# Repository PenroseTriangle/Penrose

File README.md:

The Penrose Triangle
====================

http://penrosetriangle.com/wordpress/

Hardware and software for the Penrose Triangle, a 2013 Burning Man Honorarium Project.

pcb: Eagle PCB layouts, etc.

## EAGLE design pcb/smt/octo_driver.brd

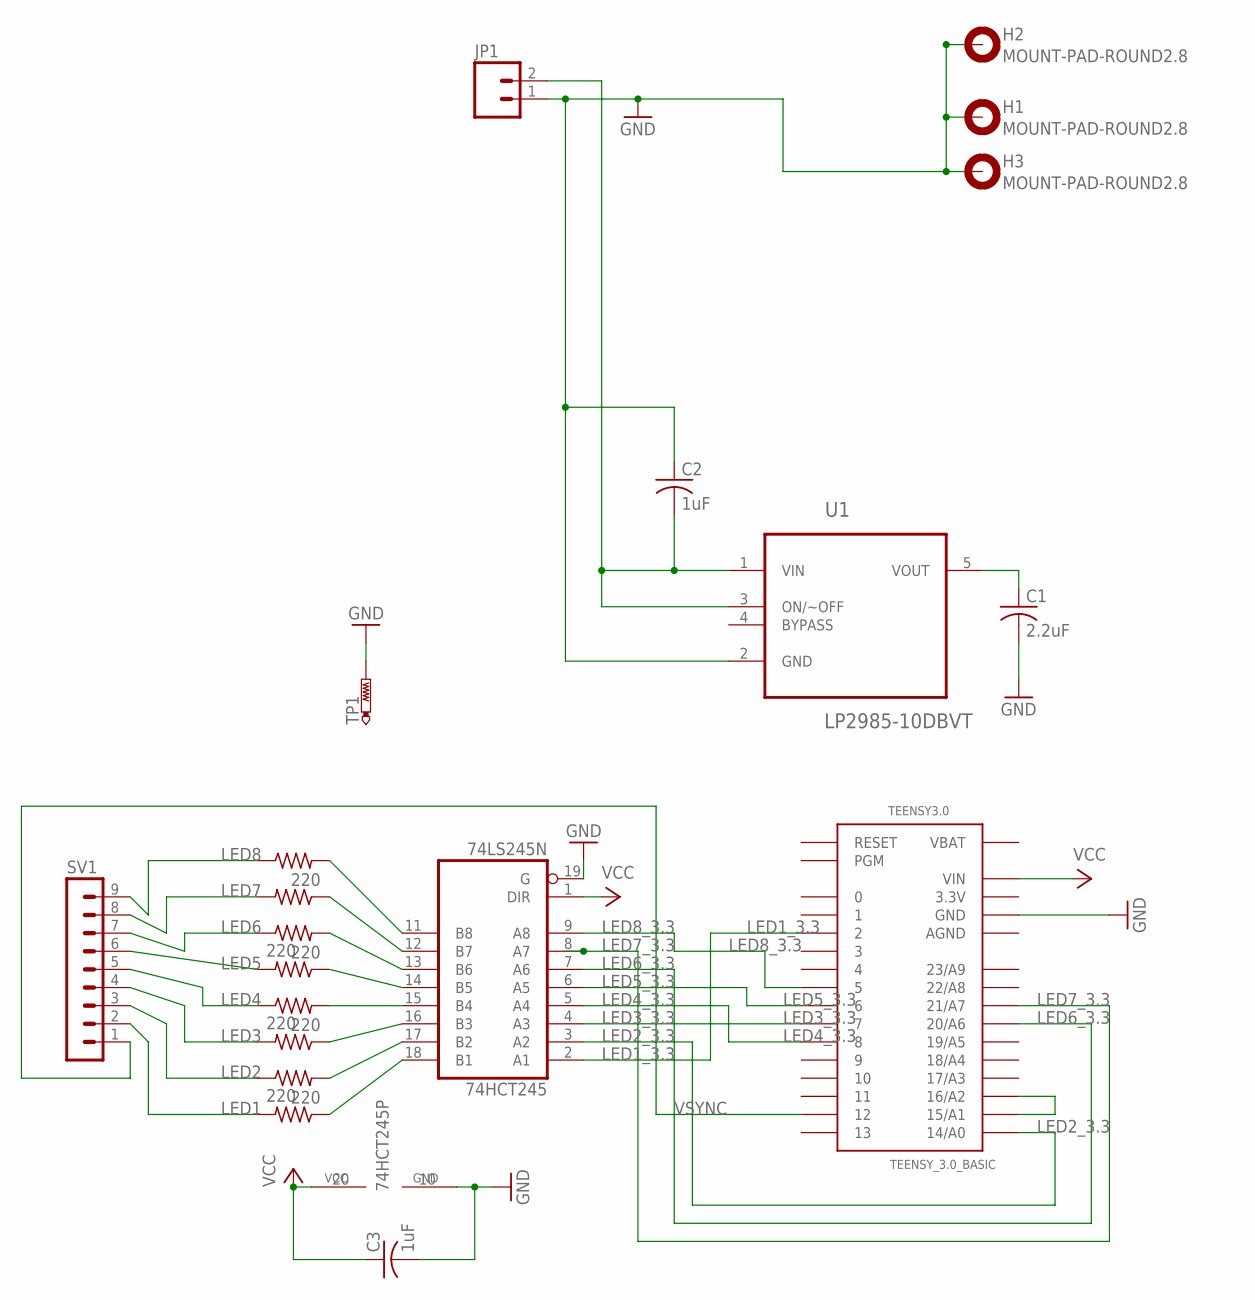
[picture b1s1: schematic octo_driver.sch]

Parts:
74HCT245: 74LS245N; DIL20
C1: 2.2uF; C0805
C2, C3: 1uF; C0805
H1, H2, H3: MOUNT-PAD-ROUND2.8; 2,8-PAD
JP1: 1X02
RLED1, RLED8, RLED9, RLED10, RLED11, RLED12, RLED13, RLED14: 220; R0805
SV1: MA09-1
TEENSY3.0: TEENSY_3.0_BASIC
TP1: PTR1B2,54; B2,54
U1: LP2985-10DBVT; SOT95P280X145-5N

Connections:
3.3V: TEENSY3.0.3.3V, TEENSY3.0.3.3V1 (3.3V)
AGND: TEENSY3.0.AGND
GND: 74HCT245.10 (GND), 74HCT245.19 (G), C1.2, C2.1, C3.2, H1.B2,8, H2.B2,8, H3.B2,8, JP1.1, TEENSY3.0.GND, TEENSY3.0.GND1 (GND), TP1.TP, U1.2 (GND)
LED1: RLED14.2, SV1.2
LED1_3.3: 74HCT245.2 (A1), TEENSY3.0.2
LED2: RLED13.1, SV1.3
LED2_3.3: 74HCT245.3 (A2), TEENSY3.0.14/A0
LED3: RLED12.2, SV1.4
LED3_3.3: 74HCT245.4 (A3), TEENSY3.0.7
LED4: RLED11.1, SV1.5
LED4_3.3: 74HCT245.5 (A4), TEENSY3.0.8
LED5: RLED10.2, SV1.6
LED5_3.3: 74HCT245.6 (A5), TEENSY3.0.6
LED6: RLED9.1, SV1.7
LED6_3.3: 74HCT245.7 (A6), TEENSY3.0.20/A6
LED7: RLED8.2, SV1.8
LED7_3.3: 74HCT245.8 (A7), TEENSY3.0.21/A7
LED8: RLED1.1, SV1.9
LED8_3.3: 74HCT245.9 (A8), TEENSY3.0.5
unnamed: C2.2, JP1.2, U1.1 (VIN), U1.3 (ON/~OFF)
unnamed: C1.1, U1.5 (VOUT)
unnamed: TEENSY3.0.15/A1, TEENSY3.0.16/A2
unnamed: 74HCT245.11 (B8), RLED1.2
unnamed: 74HCT245.12 (B7), RLED8.1
unnamed: 74HCT245.13 (B6), RLED9.2
unnamed: 74HCT245.14 (B5), RLED10.1
unnamed: 74HCT245.15 (B4), RLED11.2
unnamed: 74HCT245.16 (B3), RLED12.1
unnamed: 74HCT245.17 (B2), RLED13.2
unnamed: 74HCT245.18 (B1), RLED14.1
VBAT: TEENSY3.0.VBAT
VCC: 74HCT245.1 (DIR), 74HCT245.20 (VCC), C3.1, TEENSY3.0.VIN
VSYNC: SV1.1, TEENSY3.0.12

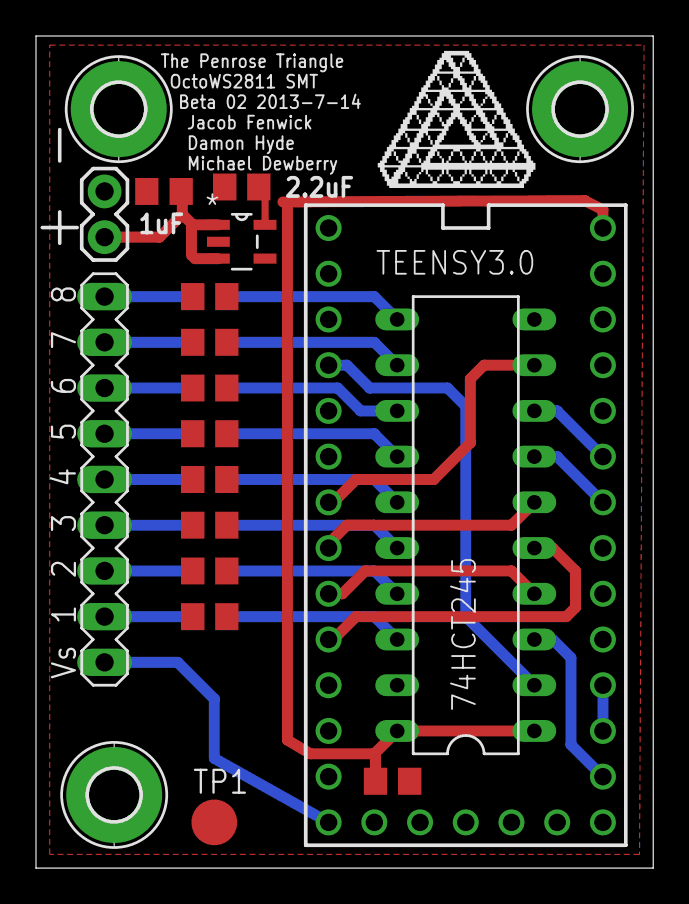
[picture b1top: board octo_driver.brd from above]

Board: 2 copper layers, 34.3 x 46.2 mm, 22 parts (0 on the bottom side), 31 nets.

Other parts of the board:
U$1: PENROSELOGO_LOWDPI
U$2: PENROSELOGO_1.75IN

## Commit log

2013-06-08 Initialize repo with driver board
2013-06-08 Nudge PCB logo a bit; add Eagle .gitignore
2013-06-08 Lower DPI logo
2013-06-09 Even lower res logo, 200dpi for OSHPark
2013-06-09 changed the text labeling the data and power connectors to all be separate vectors so they line up properly
2013-06-09 Correct logo from Hooch SVG
2013-06-09 Bottom layer silkscreen
2013-06-09 Crop bottom silkscreen to board outline, just in case
2013-07-15 modified damon's board to have art, added missing trace
2013-07-17 moved traces around and rotated resistors to get rid of warnings
2013-07-17 routed missed trace
2013-07-17 removed unnecessary trace connecting the 3.3v pins on the teensy
2013-07-17 added test pin for connecting a scope or multimeter
2013-07-17 fixed lots of warnings, general cleanup
2013-07-17 switched resistors to 0805 smt
2013-07-17 three different versions of board
2013-07-17 changed descriptions of board in file, moved folder that was incorrectly named
2013-07-17 changed descriptive text
2013-07-17 through hole regulated version added
2013-07-17 added test point
2013-07-17 removed trunk board

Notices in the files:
parts and their libraries:
SparkFun-Connectors: Licensing: CC v3.0 Share-Alike You are welcome to use this library for commercial purposes.
